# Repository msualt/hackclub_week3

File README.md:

# hackclub_week3
Stylophone redesigned for Hackclub Week 3

This is the render for my Stylophone. I've always thought they were cool, but also if you wanted to play it with your friends you were stuck to one instrument. I also noticed that they were just really bulky and large, as well as inconvenient to really carry. I designed this to be as thin and small as possible, and maybe to be able to carry it on a keychain if you really waned.

2d PCB

Schematic

BOM
| Item                             | Qty | Supplier                                       | Cost/item | Total Cost | link                                                                                                                                                                                                                                                                                                                                                                                                   |
| :------------------------------- | :-- | :--------------------------------------------- | :-------- | :--------- | :----------------------------------------------------------------------------------------------------------------------------------------------------------------------------------------------------------------------------------------------------------------------------------------------------------------------------------------------------------------------------------------------------- |
| Double Rotary Gear Potentiometer | 1   | SHENZHEN YUXIN ELECTRONIC TECHNOLOGY CO.,  LTD | $1.90     | $1.90      | https://www.aliexpress.us/item/3256808822041313.html?spm=a2g0o.cart.0.0.e67638da9SmSW7&mp=1&pdp_npi=6%40dis%21USD%21USD+1.90%21USD+1.90%21%21USD+1.90%21%21%21%402101ca8b17928095349731680e0d69%2112000047561194191%21ct%21US%212965475174%21%211%210%21&gatewayAdapt=glo2usa                                                                                                                          |
| Hc-49s                           | 1   | Shenzhen Baishun Microelectronics Co., Ltd.    | $1.38     | $1.38      | https://www.aliexpress.us/item/3256806035288739.html?spm=a2g0o.cart.0.0.e67638da9SmSW7&mp=1&pdp_npi=6%40dis%21USD%21USD+1.38%21USD+1.38%21%21USD+1.38%21%21%21%402101ca8b17928095349731680e0d69%2112000036342851380%21ct%21US%212965475174%21%211%210%21&gatewayAdapt=glo2usa                                                                                                                          |
| Mini Speaker                     | 1   | Eiechip                                        | $3.85     | $3.85      | https://www.aliexpress.us/item/3256809614662750.html?spm=a2g0o.cart.0.0.e67638da0BVdCW&mp=1&pdp_npi=6%40dis%21USD%21USD+7.71%21USD+3.85%21%21USD+3.85%21%21%21%40210328c017928097057944617e1079%2112000050209670104%21ct%21US%212965475174%21%211%210%21&gatewayAdapt=glo2usa                                                                                                                          |
| 0603 Capacitors                  | 1   | PUMUDSY                                        | $3.39     | $3.39      | https://www.aliexpress.us/item/3256809274295297.html?spm=a2g0o.cart.0.0.e67638da0BVdCW&mp=1&sourceType=570&pdp_npi=6%40dis%21USD%21USD+7.26%21USD+3.39%21%21USD+3.39%21%21%21%40210328c017928097802167263e1079%2112000049174426596%21ct%21US%212965475174%21%211%210%21&pdp_ext_f=%7B%22cart2PdpParams%22%3A%7B%22sourceType%22%3A%22570%22%2C%22cartSource%22%3A%22main%22%7D%7D&gatewayAdapt=glo2usa |
| UCM0J221MCL1GS                   | 4   | Nichicon                                       | $0.56     | $2.24      | https://www.digikey.com/en/products/detail/nichicon/UCM0J221MCL1GS/4991824                                                                                                                                                                                                                                                                                                                             |
| MCP23017-E/SO                    | 4   | Microchip Technology                           | $1.62     | $6.48      | https://www.digikey.com/en/products/detail/microchip-technology/MCP23017-E-SO/894271https://www.digikey.com/en/products/detail/microchip-technology/MCP23017-E-SO/894271                                                                                                                                                                                                                               |
| ATMEGA32U4-AU                    | 4   | Microchip Technology                           | $5.29     | $21.16     | https://www.digikey.com/en/products/detail/microchip-technology/ATMEGA32U4-AU/1914602                                                                                                                                                                                                                                                                                                                  |
| LM386N-1                         | 1   | Shenzhen crador Technology Co., Ltd.           | $0.99     | $0.99      | https://www.aliexpress.us/item/3256806565410890.html?spm=a2g0o.cart.0.0.633638daoFHugw&mp=1&pdp_npi=6%40dis%21USD%21USD+1.60%21USD+0.99%21%21USD+0.99%21%21%21%402101e5ab17928103719767913e0ded%2112000038184697503%21ct%21US%212965475174%21%211%210%21&gatewayAdapt=glo2usa                                                                                                                          |
| PCB                              | 1   | JLCPCB                                         | $3.30     | $3.30      | https://jlcpcb.com                                                                                                                                                                                                                                                                                                                                                                                     |
| Multimeter Probe                 | 1   | XINGWEIQIANG-09                                | $0.99     | $0.99      | https://www.aliexpress.us/item/3256805754330375.html?spm=a2g0o.cart.0.0.730538dafzkk7q&mp=1&pdp_npi=6%40dis%21USD%21USD+1.78%21USD+1.78%21%21USD+1.78%21%21%21%40210328df17928110851318123e0f2b%2112000034961777940%21ct%21US%212965475174%21%211%210%21&gatewayAdapt=glo2usa                                                                                                                          |
| Multimeter Probe                 | 1   | ThinkingLeader                                 | $0.99     | $0.99      | https://www.aliexpress.us/item/2251832802518998.html?spm=a2g0o.cart.0.0.730538dafzkk7q&mp=1&pdp_npi=6%40dis%21USD%21USD+1.32%21USD+1.32%21%21USD+1.32%21%21%21%40210328df17928110851318123e0f2b%2166819747268%21ct%21US%212965475174%21%211%210%21&gatewayAdapt=glo2usa                                                                                                                                |
| 1x6 Pogo Pins                    | 1   | RTLECS Precision                               | $3.83     | $3.83      | https://www.aliexpress.us/item/3256804960956555.html?spm=a2g0o.cart.0.0.5de638daQSWFBy&mp=1&pdp_npi=6%40dis%21USD%21USD+3.83%21USD+3.83%21%21USD+3.32%21%21%21%402101e81117928119416688503e0e01%2112000041502007192%21ct%21US%212965475174%21%211%210%21&gatewayAdapt=glo2usa                                                                                                                          |
| Estimated total shipping         | 1   |                                                |           | $8.26      |                                                                                                                                                                                                                                                                                                                                                                                                        |

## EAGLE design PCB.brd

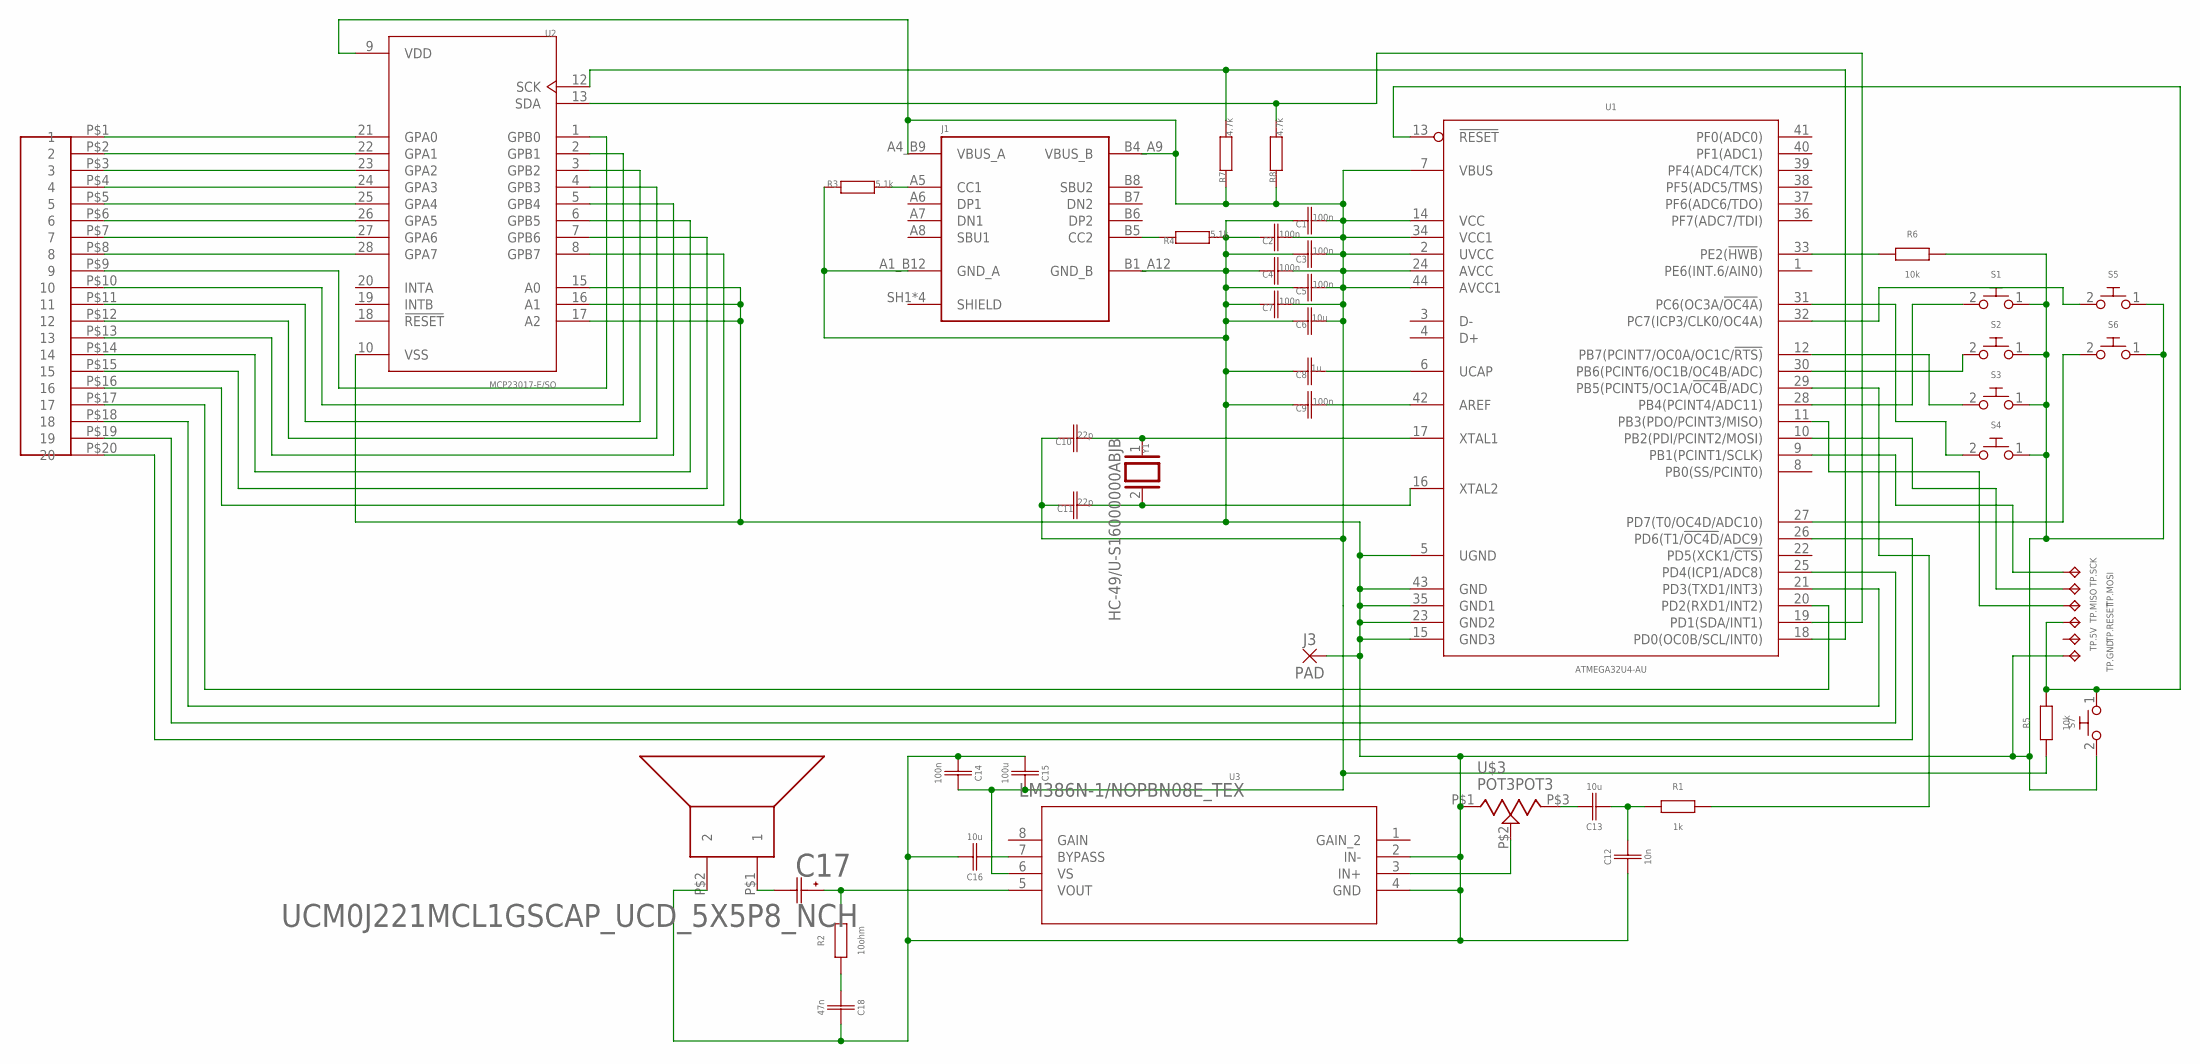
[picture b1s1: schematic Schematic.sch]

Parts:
C1, C2, C3, C4, C5, C7, C9, C14: 100n; CAPC1608X85
C6, C13, C16: 10u; CAPC1608X85
C8: 1u; CAPC1608X85
C10, C11: 22p; CAPC1608X85
C12: 10n; CAPC1608X85
C15: 100u; CAPC1608X85
C17: UCM0J221MCL1GSCAP_UCD_5X5P8_NCH; CAP_UCD_5X5P8_NCH
C18: 47n; CAPC1608X85
J1: USB4215-03-A_REVAUSB4115-03-C_REVA; GCT_USB4215-03-A_REVA
J3: PAD; 2.54/1.0
R1: 1k; RESC1608X60
R2: 10ohm; RESC1608X60
R3, R4: 5.1k; RESC1608X60
R5, R6: 10k; RESC1608X60
R7, R8: 4.7k; RESC1608X60
S1, S2, S3, S4, S5, S6, S7: B3U-X000B3U-1000P(M)1000P(M); B3U-1000P(M)
TP.5V, TP.GND, TP.MISO, TP.MOSI, TP.RESET, TP.SCK: TPTP127R; TP127R
U1: ATMEGA32U4-AU; QFP80P1200X1200X120-44
U2: MCP23017-E/SO; SOIC127P1030X265-28N
U3: LM386N-1/NOPBN08E_TEX; N08E_TEX
U$1: STYLOPHONEPAD; STYLOPHONEPCB
U$2: 23072307; 2307
U$3: POT3POT3; POT3
Y1: HC-49/U-S16000000ABJB; XTAL_HC49P488W43L1150T466H350

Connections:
5V: C1.1, C2.1, C3.1, C4.1, C5.1, C6.1, C7.1, C10.2, C11.2, C14.2, C15.2, J1.A4_B9 (VBUS_A), J1.B4_A9 (VBUS_B), R5.1, R7.1, R8.1, U1.2 (UVCC), U1.7 (VBUS), U1.14 (VCC), U1.24 (AVCC), U1.34 (VCC1), U1.44 (AVCC1), U2.9 (VDD), U3.6 (VS)
GND: C1.2, C2.2, C3.2, C4.2, C5.2, C6.2, C7.2, C8.2, C9.2, C12.1, C14.1, C15.1, C16.2, C18.2, J1.A1_B12 (GND_A), J1.B1_A12 (GND_B), J3.1, R3.2, R4.1, R6.2, S1.1, S2.1, S3.1, S4.1, S5.1, S6.1, S7.2, TP.GND.TP, U1.5 (UGND), U1.15 (GND3), U1.23 (GND2), U1.35 (GND1), U1.43 (GND), U2.10 (VSS), U2.15 (A0), U2.16 (A1), U2.17 (A2), U3.2 (IN-), U3.4 (GND), U$2.P$2 (2), U$3.P$1 (CCW)
unnamed: R7.2, U1.18 (PD0(OC0B/SCL/INT0)), U2.12 (SCK)
unnamed: R8.2, U1.19 (PD1(SDA/INT1)), U2.13 (SDA)
unnamed: U2.21 (GPA0), U$1.P$1 (1)
unnamed: U2.22 (GPA1), U$1.P$2 (2)
unnamed: U2.23 (GPA2), U$1.P$3 (3)
unnamed: U2.24 (GPA3), U$1.P$4 (4)
unnamed: U2.25 (GPA4), U$1.P$5 (5)
unnamed: U2.26 (GPA5), U$1.P$6 (6)
unnamed: U2.27 (GPA6), U$1.P$7 (7)
unnamed: U2.28 (GPA7), U$1.P$8 (8)
unnamed: U2.1 (GPB0), U$1.P$9 (9)
unnamed: U2.2 (GPB1), U$1.P$10 (10)
unnamed: U2.3 (GPB2), U$1.P$11 (11)
unnamed: U2.4 (GPB3), U$1.P$12 (12)
unnamed: U2.5 (GPB4), U$1.P$13 (13)
unnamed: U2.6 (GPB5), U$1.P$14 (14)
unnamed: U2.7 (GPB6), U$1.P$15 (15)
unnamed: U2.8 (GPB7), U$1.P$16 (16)
unnamed: U1.20 (PD2(RXD1/INT2)), U$1.P$17 (17)
unnamed: U1.21 (PD3(TXD1/INT3)), U$1.P$18 (18)
unnamed: U1.25 (PD4(ICP1/ADC8)), U$1.P$19 (19)
unnamed: U1.26 (PD6(T1/!OC4D!/ADC9)), U$1.P$20 (20)
unnamed: S1.2, U1.28 (PB4(PCINT4/ADC11))
unnamed: S2.2, U1.30 (PB6(PCINT6/OC1B/OC4B/ADC))
unnamed: S3.2, U1.12 (PB7(PCINT7/OC0A/OC1C/!RTS))
unnamed: S4.2, U1.31 (PC6(OC3A/!OC4A!))
unnamed: S5.2, U1.32 (PC7(ICP3/CLK0/OC4A))
unnamed: S6.2, U1.27 (PD7(T0/OC4D/ADC10))
unnamed: C18.1, R2.1
unnamed: R1.2, U1.29 (PB5(PCINT5/OC1A/!OC4B!/ADC))
unnamed: C12.2, C13.1, R1.1
unnamed: C13.2, U$3.P$3 (CW)
unnamed: U3.3 (IN+), U$3.P$2 (WIPER)
unnamed: C16.1, U3.7 (BYPASS)
unnamed: C9.1, U1.42 (AREF)
unnamed: C11.1, U1.16 (XTAL2), Y1.2
unnamed: C17.1, R2.2, U3.5 (VOUT)
unnamed: J1.B5 (CC2), R4.2
unnamed: J1.A5 (CC1), R3.1
unnamed: C8.1, U1.6 (UCAP)
unnamed: R6.1, U1.33 (PE2(!HWB!))
unnamed: TP.SCK.TP, U1.9 (PB1(PCINT1/SCLK))
unnamed: TP.MOSI.TP, U1.10 (PB2(PDI/PCINT2/MOSI))
unnamed: TP.MISO.TP, U1.11 (PB3(PDO/PCINT3/MISO))
unnamed: R5.2, S7.1, TP.RESET.TP, U1.13 (!RESET)
unnamed: C10.1, U1.17 (XTAL1), Y1.1
unnamed: C17.2, U$2.P$1 (1)

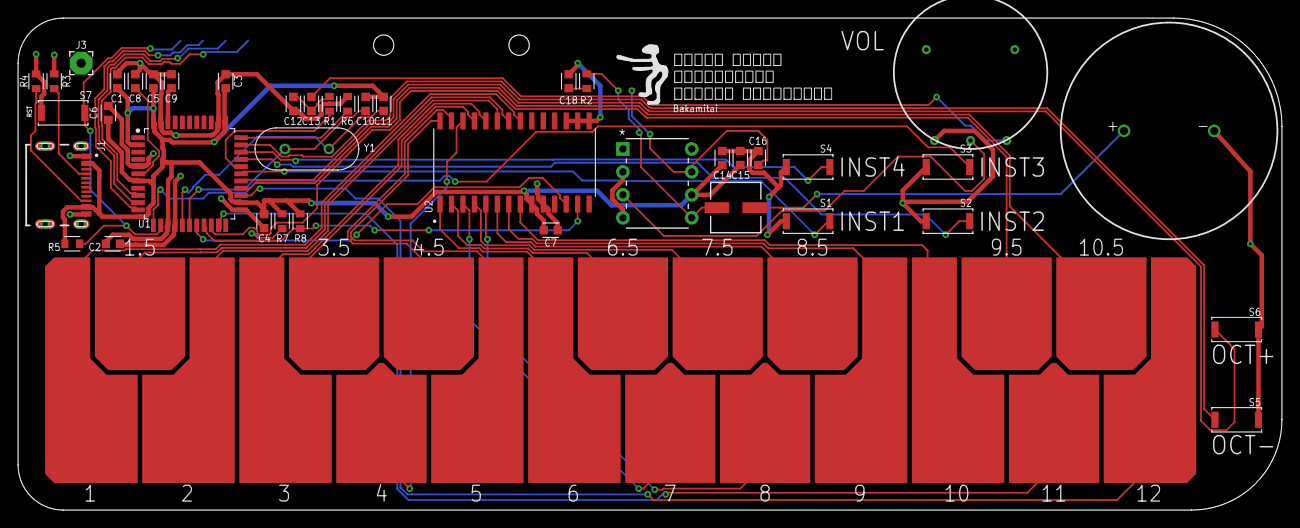
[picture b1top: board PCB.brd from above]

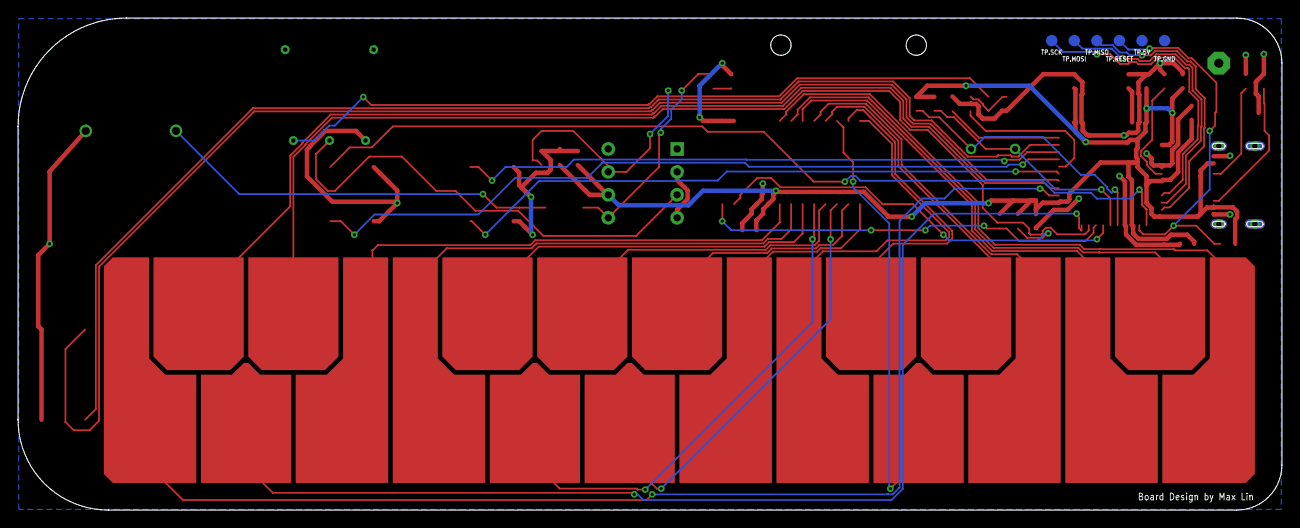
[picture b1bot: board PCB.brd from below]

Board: 2 copper layers, 140.0 x 54.5 mm, 48 parts (6 on the bottom side), 49 nets.

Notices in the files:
parts and their libraries:
COPYRIGHT: Copyright (C) 2026 Ultra Librarian. All rights reserved.
